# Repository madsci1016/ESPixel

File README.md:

# ESPixel
ESP8266 based WIFI pixel drivers. A design for both GECE (GE Color Effects) and standard WS2811 pixels. 

This work is licensed under a Creative Commons Attribution-NonCommercial 4.0 International License. This work is distributed in the hope that it will be useful, but WITHOUT ANY WARRANTY; without even the implied warranty of MERCHANTABILITY or FITNESS FOR A PARTICULAR PURPOSE.

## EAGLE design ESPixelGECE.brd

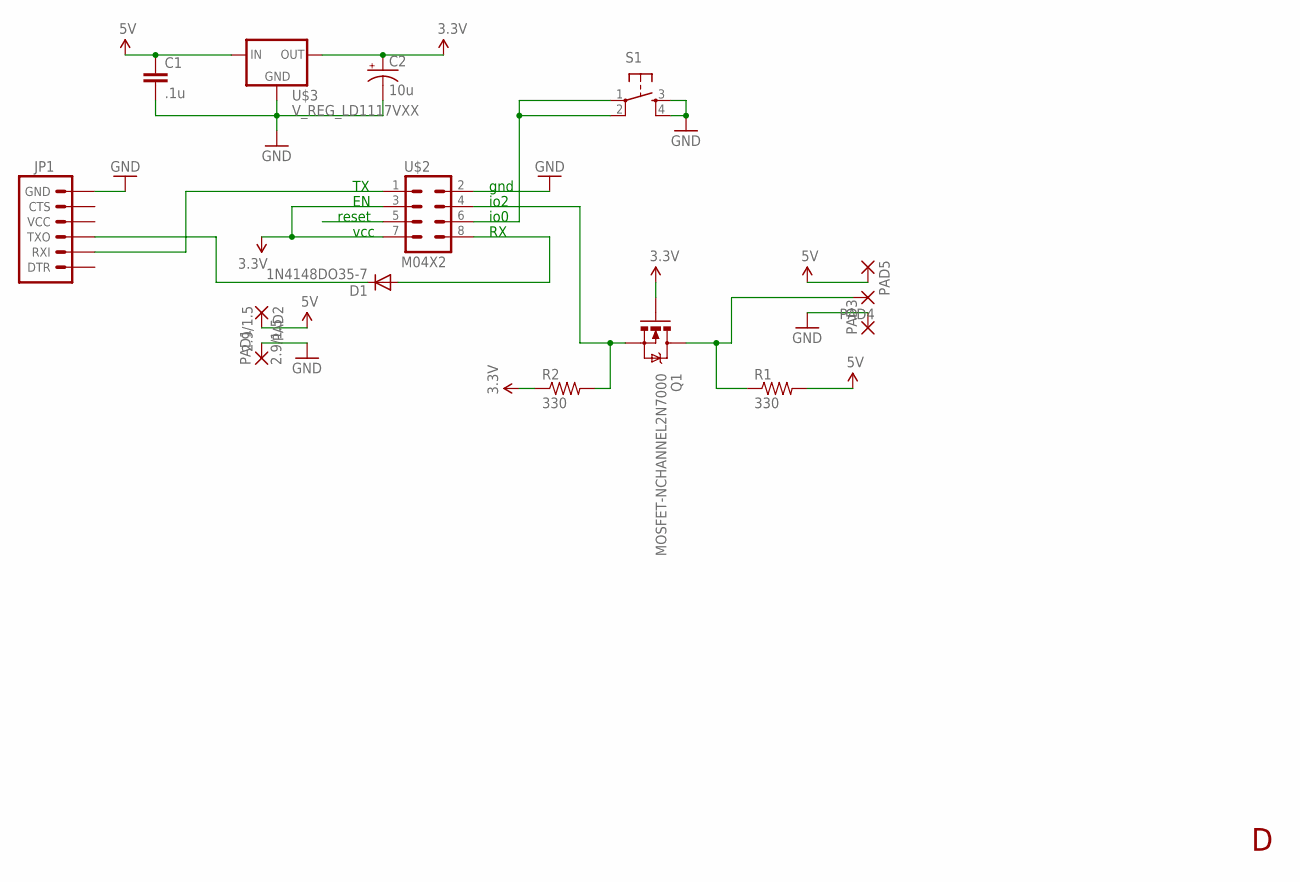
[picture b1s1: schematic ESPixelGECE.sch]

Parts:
C1: .1u; CAP-PTH-SMALLEZ
C2: 10u; CPOL-RADIAL-10UF-25V
D1: 1N4148DO35-7; DO35-7
JP1: ARDUINO_SERIAL_PROGRAMLOCK; 1X06_LOCK
PAD1, PAD2: 2.9/1.5
PAD3, PAD4, PAD5: 2,15/1,0
Q1: MOSFET-NCHANNEL2N7000; TO-92
R1, R2: 330; AXIAL-0.3EZ
S1: TAC_SWITCHPTH; TACTILE-PTH
U$2: M04X2; 2X4
U$3: V_REG_LD1117VXX; 78XXL

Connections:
3.3V: C2.1 (+), Q1.2 (G), R2.P$1 (1), U$2.3, U$2.7, U$3.GND (OUT)
5V: C1.1, PAD2.1, PAD5.1, R1.P$2 (2), U$3.OUT (IN)
GND: C1.2, C2.2 (-), JP1.6 (GND), PAD1.1, PAD3.1, S1.3, S1.4, U$2.2, U$3.IN (GND)
unnamed: JP1.2 (RXI), U$2.1
unnamed: D1.A, U$2.8
unnamed: PAD4.1, Q1.3 (D), R1.P$1 (1)
unnamed: S1.1, S1.2, U$2.6
unnamed: Q1.1 (S), R2.P$2 (2), U$2.4
unnamed: D1.C, JP1.3 (TXO)

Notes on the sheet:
reset
vcc
gnd
io2
io0

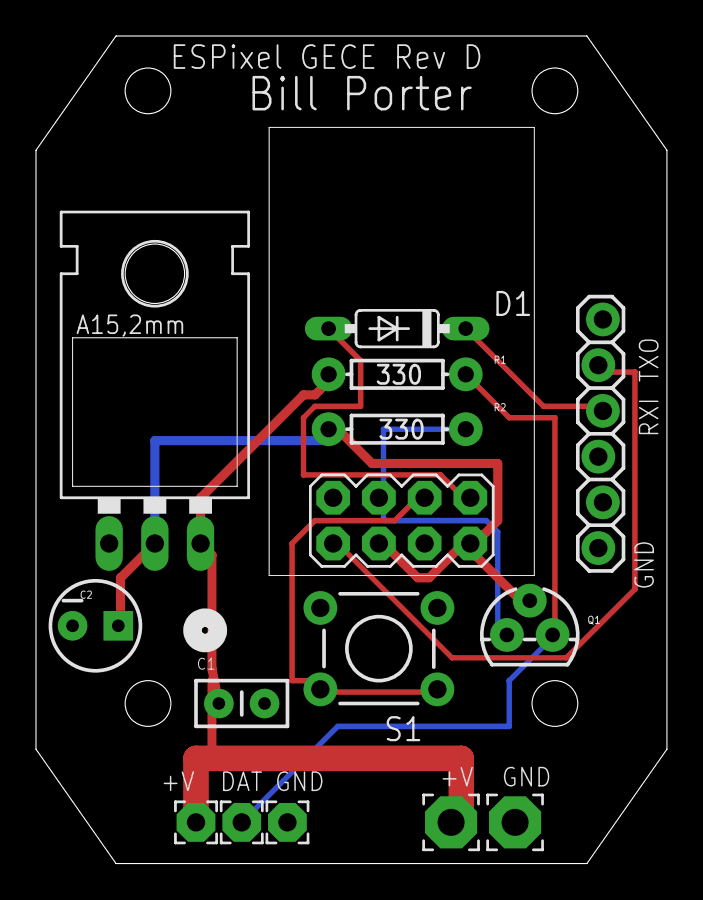
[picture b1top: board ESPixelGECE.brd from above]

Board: 2 copper layers, 35.1 x 46.0 mm, 15 parts (0 on the bottom side), 9 nets.

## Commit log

2015-08-05 Added GECE design
2015-08-06 Added Diode to GECE and added WS2811 version
2015-11-01 Added BOMs, SEEED cam
2015-12-13 ESPixel now 12V or 5V
    Added 5V reg for 12V pixel operation.
2015-12-13 Clean up
2015-12-26 Added ESPixel Seeed Cam
2015-12-26 Updated ESPixel BOM with enclosure and glands

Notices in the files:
parts and their libraries:
SparkFun-Capacitors: Licensing: Creative Commons ShareAlike 4.0 International - https://creativecommons.org/licenses/by-sa/4.0
